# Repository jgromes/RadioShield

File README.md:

# Arduino Radio Shield

## "The Swiss Army Knife of Arduino Radio shields" - [Hackaday.com blog](https://hackaday.com/2018/07/28/why-have-only-one-radio-when-you-can-have-two/)

### Designed for use with [RadioLib](https://github.com/jgromes/RadioLib) - Universal wireless communication library for Arduino.

## Revision C
The latest hardware revision, compatible with both 5V and 3.3V Arduino boards. The entire project was also rebranded as Radio Shield!

Additional modules:
* **SIM800C** GSM module
* **CC1101** FSK module
* **nRF24L01** 2.4 GHz module

## Revision B
Added some improvements over rev. A, such as improved Arduino Mega support and interrupt selection pin header.

## Revision A
After a first few prototypes, rev. A is the first fully tested and working shield.  
Supported modules:
* **ESP8266** WiFi module
* **HC-05** Bluetooth module
* **RFM69** FSK/OOK radio module
* **SX127x** series LoRa modules - including SX1272, SX1276 and SX1278
* **XBee** modules (S2B)

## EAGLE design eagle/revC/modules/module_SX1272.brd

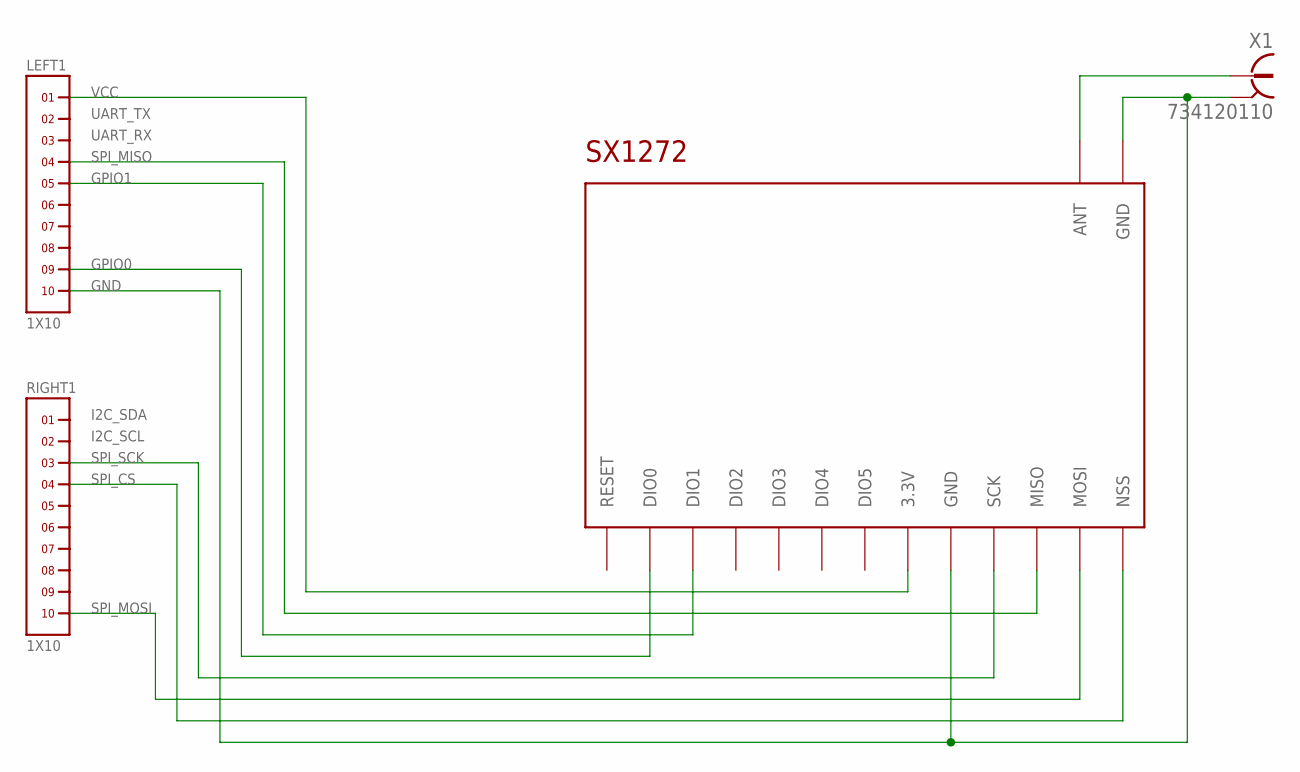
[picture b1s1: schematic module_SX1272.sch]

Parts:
LEFT1: 1X10
RIGHT1: 1X10
U$1: SX1272
X1: 734120110

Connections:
GND: LEFT1.10, U$1.GND@1 (GND), U$1.GND@2 (GND), X1.S@1 (2), X1.S@2 (2), X1.S@3 (2)
unnamed: U$1.ANT, X1.1
unnamed: LEFT1.9, U$1.DIO0
unnamed: RIGHT1.10, U$1.MOSI
unnamed: RIGHT1.4, U$1.NSS
unnamed: RIGHT1.3, U$1.SCK
unnamed: LEFT1.5, U$1.DIO1
unnamed: LEFT1.4, U$1.MISO
VCC: LEFT1.1, U$1.3.3V

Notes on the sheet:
VCC
UART_TX
UART_RX
SPI_MISO
GPIO1
GND
GPIO0
SPI_MOSI
I2C_SDA
I2C_SCL
SPI_SCK
SPI_CS

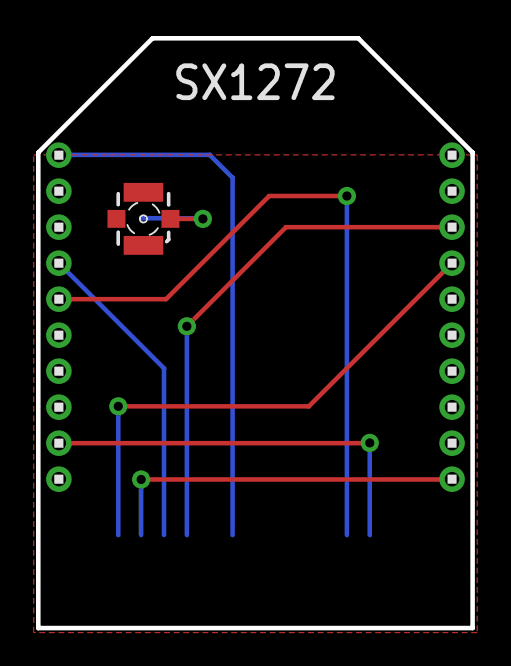
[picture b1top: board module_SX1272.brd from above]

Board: 2 copper layers, 24.1 x 32.8 mm, 4 parts (1 on the bottom side), 9 nets.

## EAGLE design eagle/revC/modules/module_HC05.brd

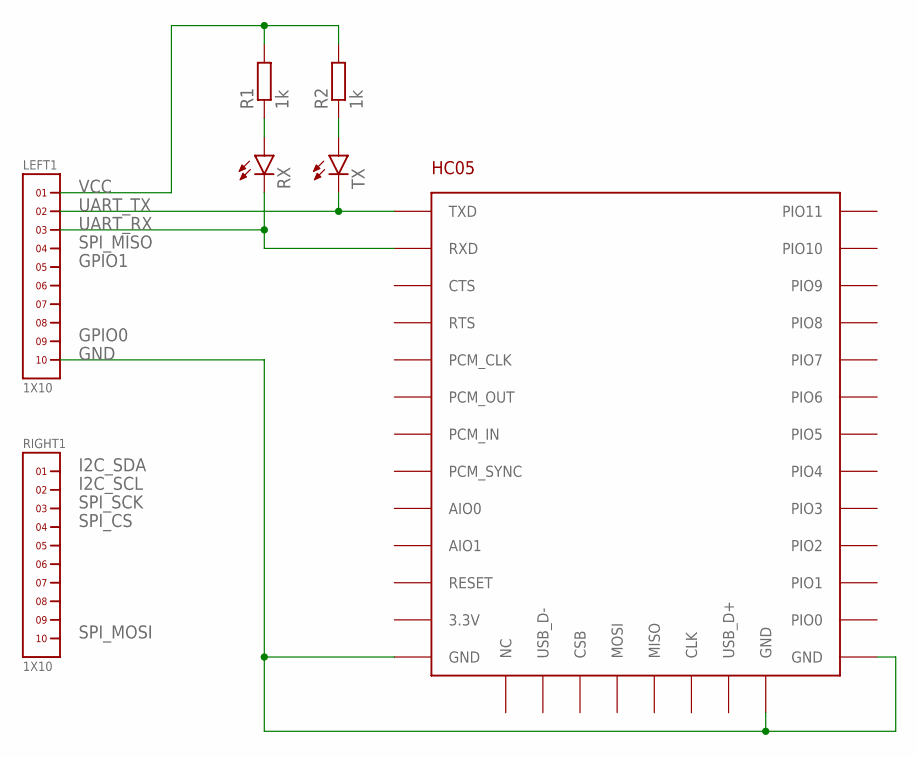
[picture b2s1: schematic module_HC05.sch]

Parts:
LEFT1: 1X10
R1, R2: 1k; R0603
RIGHT1: 1X10
RX: LEDCHIP-LED0603; CHIP-LED0603
TX: LEDCHIP-LED0603; CHIP-LED0603
U$1: HC05

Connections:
GND: LEFT1.10, U$1.GND@1 (GND), U$1.GND@2 (GND), U$1.GND@3 (GND)
unnamed: R2.1, TX.A
unnamed: R1.1, RX.A
unnamed: LEFT1.2, TX.C, U$1.TX (TXD)
unnamed: LEFT1.3, RX.C, U$1.RX (RXD)
VCC: LEFT1.1, R1.2, R2.2

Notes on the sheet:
VCC
I2C_SDA
I2C_SCL
SPI_SCK
SPI_CS
SPI_MOSI
UART_TX
UART_RX
SPI_MISO
GPIO1
GPIO0
GND

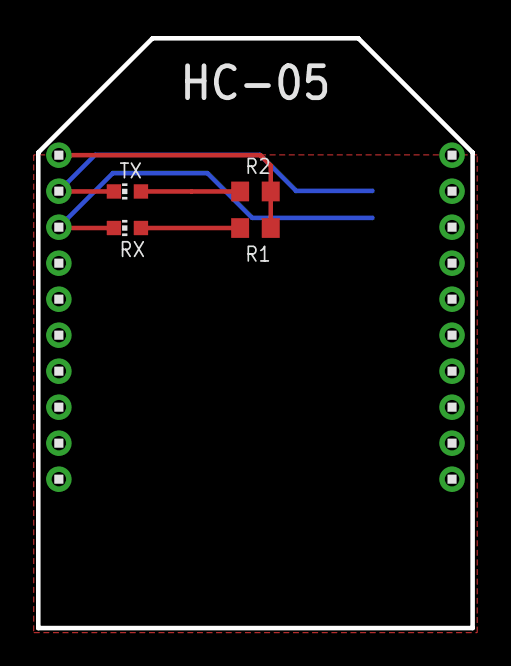
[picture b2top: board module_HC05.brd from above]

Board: 2 copper layers, 24.1 x 32.8 mm, 7 parts (1 on the bottom side), 6 nets.

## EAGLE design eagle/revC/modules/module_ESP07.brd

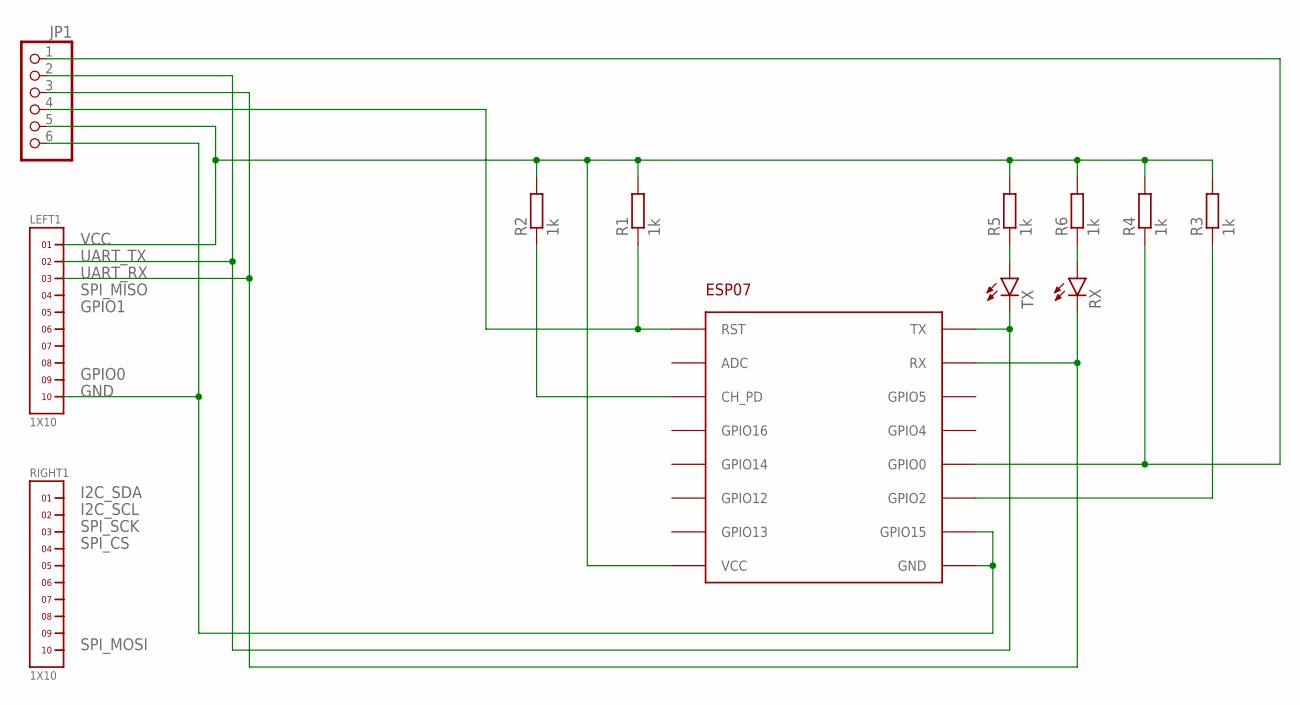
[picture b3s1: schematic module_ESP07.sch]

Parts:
JP1: PINHD-1X6; 1X06
LEFT1: 1X10
R1, R2, R3, R4, R5, R6: 1k; R0603
RIGHT1: 1X10
RX: LEDCHIPLED_0603; CHIPLED_0603
TX: LEDCHIPLED_0603; CHIPLED_0603
U$1: ESP-07; ESP07

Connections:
GND: JP1.6, LEFT1.10, U$1.GND, U$1.GPIO15
GPIO0: JP1.1, R4.1, U$1.GPIO0
unnamed: R6.1, RX.A
unnamed: R5.1, TX.A
unnamed: R2.1, U$1.CH_PD
unnamed: R3.1, U$1.GPIO2
RST: JP1.4, R1.1, U$1.RST
UART_RX: JP1.3, LEFT1.3, RX.C, U$1.RX
UART_TX: JP1.2, LEFT1.2, TX.C, U$1.TX
VCC: JP1.5, LEFT1.1, R1.2, R2.2, R3.2, R4.2, R5.2, R6.2, U$1.VCC

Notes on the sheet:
VCC
I2C_SDA
I2C_SCL
SPI_SCK
SPI_CS
SPI_MOSI
UART_TX
UART_RX
SPI_MISO
GPIO1
GPIO0
GND

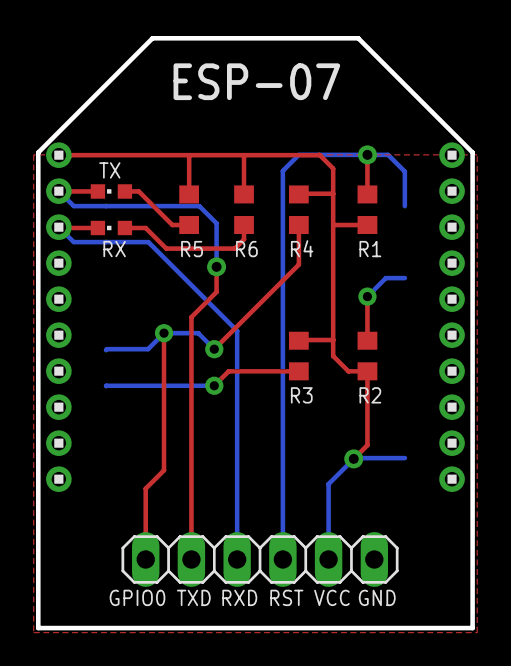
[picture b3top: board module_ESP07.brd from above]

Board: 2 copper layers, 24.1 x 32.8 mm, 12 parts (1 on the bottom side), 10 nets.

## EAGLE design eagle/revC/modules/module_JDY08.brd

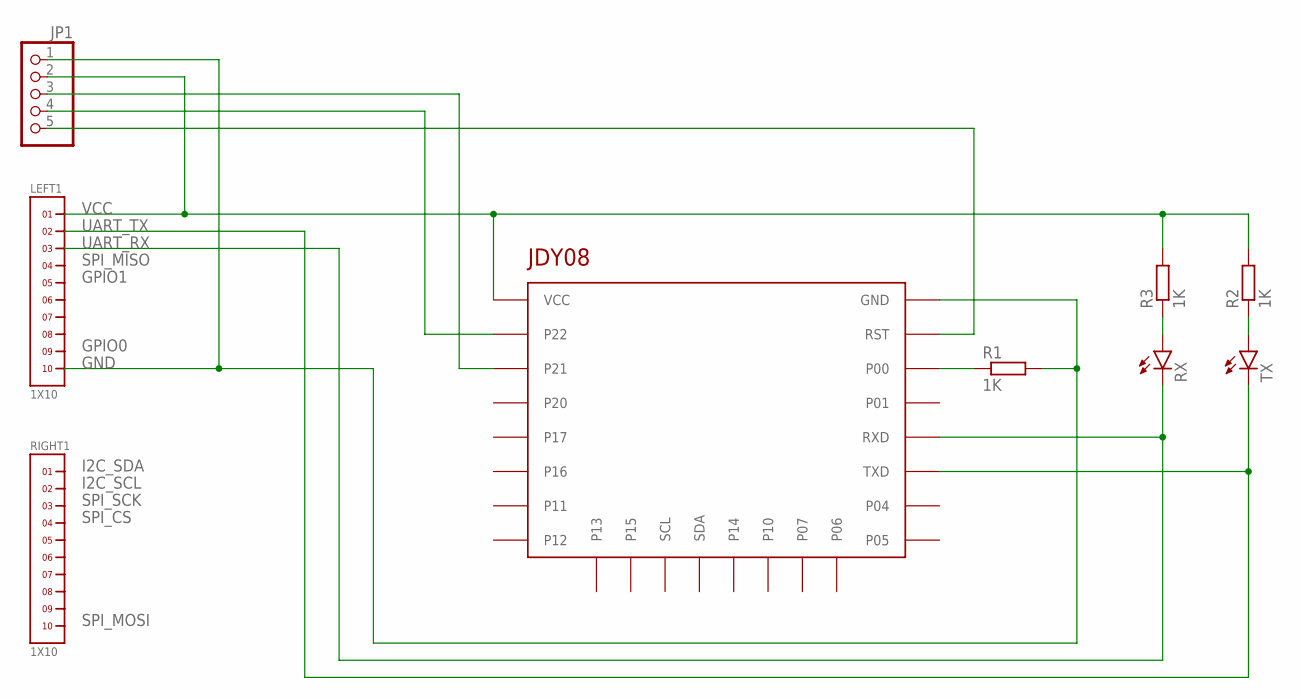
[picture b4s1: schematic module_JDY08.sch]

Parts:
JP1: PINHD-1X5; 1X05
LEFT1: 1X10
R1, R2, R3: 1K; R0603
RIGHT1: 1X10
RX: LEDCHIPLED_0603; CHIPLED_0603
TX: LEDCHIPLED_0603; CHIPLED_0603
U$1: JDY08

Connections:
GND: JP1.1, LEFT1.10, R1.2, U$1.GND
unnamed: JP1.5, U$1.RST
unnamed: JP1.3, U$1.P21
unnamed: JP1.4, U$1.P22
unnamed: LEFT1.3, RX.C, U$1.RXD
unnamed: R2.1, TX.A
unnamed: R3.1, RX.A
unnamed: R1.1, U$1.P00
unnamed: LEFT1.2, TX.C, U$1.TXD
VCC: JP1.2, LEFT1.1, R2.2, R3.2, U$1.VCC

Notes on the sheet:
VCC
I2C_SDA
I2C_SCL
SPI_SCK
SPI_CS
SPI_MOSI
UART_TX
UART_RX
SPI_MISO
GPIO1
GPIO0
GND

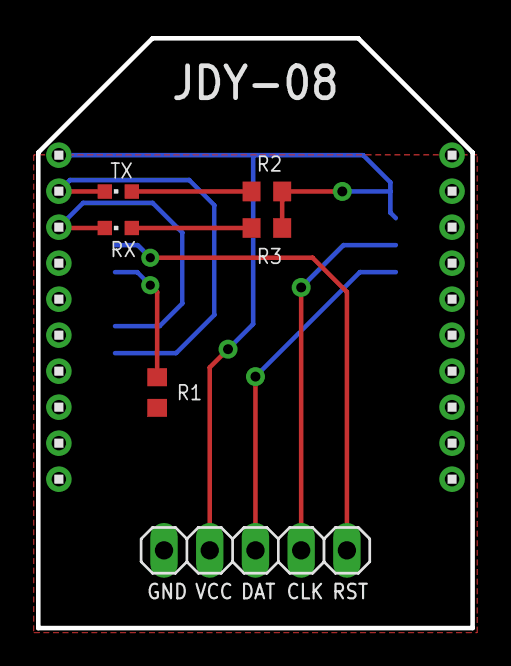
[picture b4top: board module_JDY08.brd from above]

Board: 2 copper layers, 24.1 x 32.8 mm, 9 parts (1 on the bottom side), 10 nets.

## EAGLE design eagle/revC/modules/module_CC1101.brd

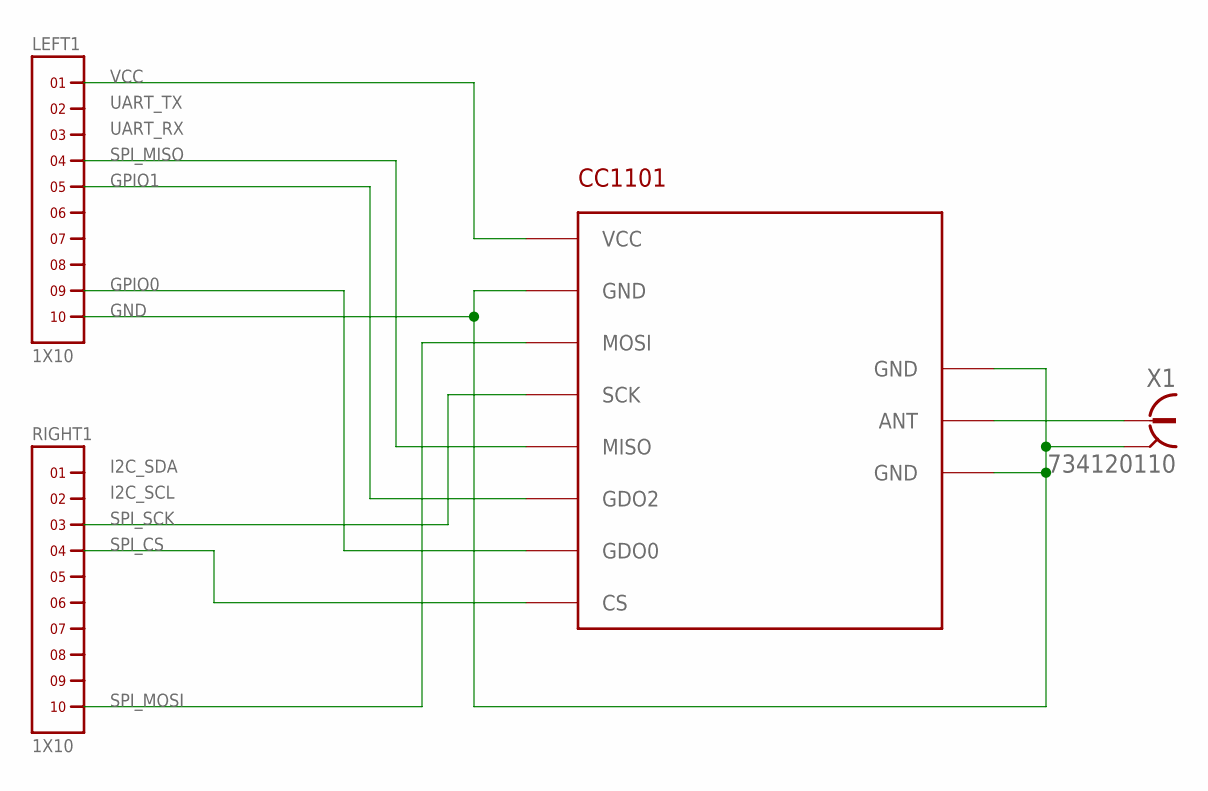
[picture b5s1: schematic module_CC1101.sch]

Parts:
CC1101: CC1101
LEFT1: 1X10
RIGHT1: 1X10
X1: 734120110

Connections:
GND: CC1101.GND@1 (GND), CC1101.GND@2 (GND), CC1101.GND@3 (GND), LEFT1.10, X1.S@1 (2), X1.S@2 (2), X1.S@3 (2)
INT0: CC1101.GDO0, LEFT1.9
INT1: CC1101.GDO2, LEFT1.5
unnamed: CC1101.ANT, X1.1
SPI_CS: CC1101.CS, RIGHT1.4
SPI_MISO: CC1101.MISO, LEFT1.4
SPI_MOSI: CC1101.MOSI, RIGHT1.10
SPI_SCK: CC1101.SCK, RIGHT1.3
VCC: CC1101.VCC, LEFT1.1

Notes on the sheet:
VCC
UART_TX
UART_RX
SPI_MISO
GPIO1
GND
GPIO0
SPI_MOSI
I2C_SDA
I2C_SCL
SPI_SCK
SPI_CS

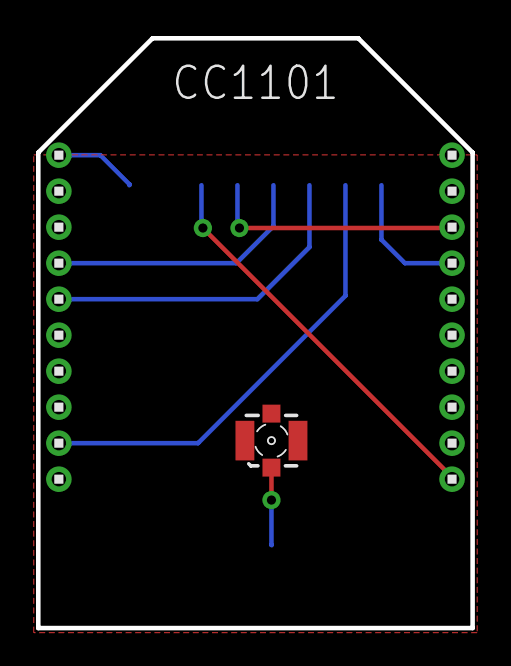
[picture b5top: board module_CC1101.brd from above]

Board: 2 copper layers, 24.1 x 32.8 mm, 4 parts (1 on the bottom side), 9 nets.

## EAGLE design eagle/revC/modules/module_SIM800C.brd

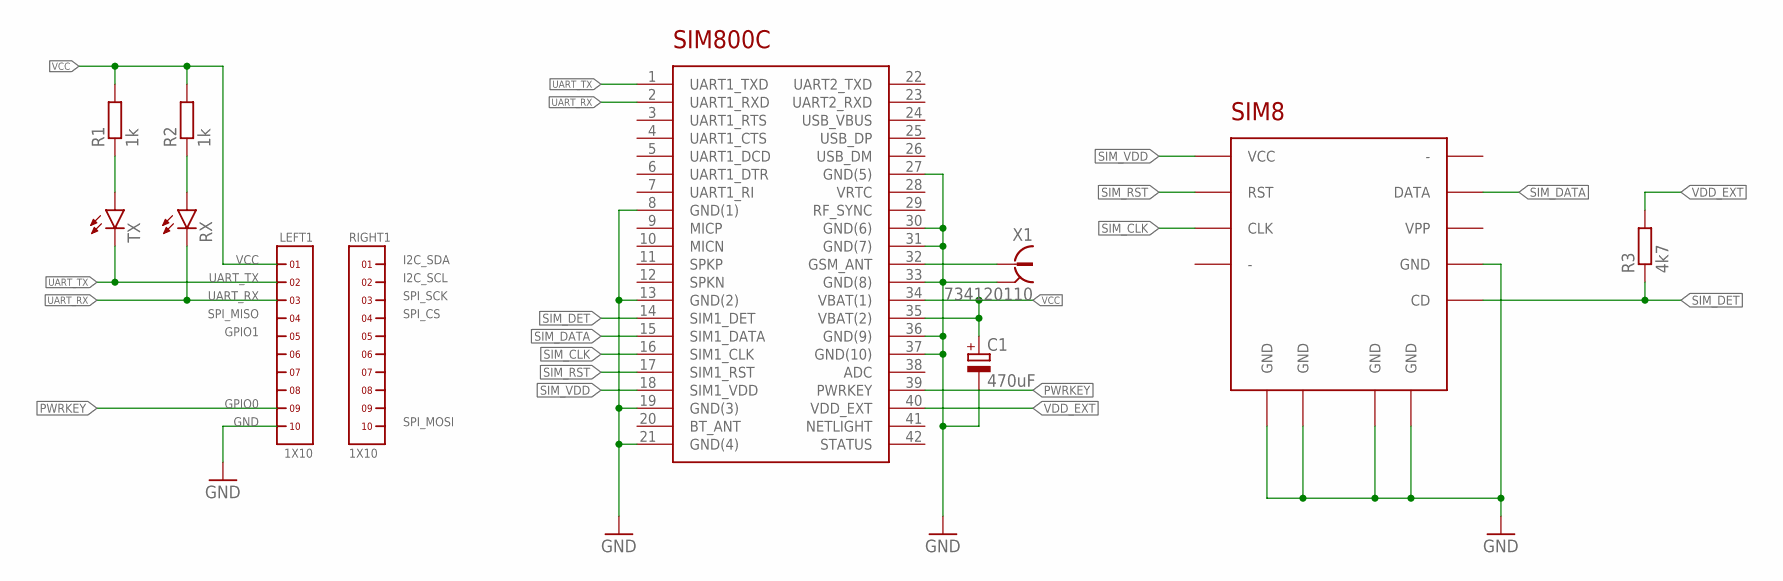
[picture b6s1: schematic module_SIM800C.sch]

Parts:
C1: 470uF; SMC_D
IC1: SIM800C
LEFT1: 1X10
R1, R2: 1k; R0603
R3: 4k7; R0603
RIGHT1: 1X10
RX: LEDCHIPLED_0603; CHIPLED_0603
TX: LEDCHIPLED_0603; CHIPLED_0603
U$2: 115Q-BCA0
X1: 734120110

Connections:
GND: C1.-, IC1.8 (GND(1)), IC1.13 (GND(2)), IC1.19 (GND(3)), IC1.21 (GND(4)), IC1.27 (GND(5)), IC1.30 (GND(6)), IC1.31 (GND(7)), IC1.33 (GND(8)), IC1.36 (GND(9)), IC1.37 (GND(10)), LEFT1.10, U$2.P$5 (GND), U$2.P$10 (GND), U$2.P$11 (GND), U$2.P$12 (GND), U$2.P$13 (GND), X1.S@1 (2), X1.S@2 (2), X1.S@3 (2)
unnamed: IC1.32 (GSM_ANT), X1.1
unnamed: R1.1, TX.A
unnamed: R2.1, RX.A
PWRKEY: IC1.39 (PWRKEY), LEFT1.9
SIM_CLK: IC1.16 (SIM1_CLK), U$2.P$3 (CLK)
SIM_DATA: IC1.15 (SIM1_DATA), U$2.P$7 (DATA)
SIM_DET: IC1.14 (SIM1_DET), R3.1, U$2.P$9 (CD)
SIM_RST: IC1.17 (SIM1_RST), U$2.P$2 (RST)
SIM_VDD: IC1.18 (SIM1_VDD), U$2.P$1 (VCC)
UART_RX: IC1.2 (UART1_RXD), LEFT1.3, RX.C
UART_TX: IC1.1 (UART1_TXD), LEFT1.2, TX.C
VCC: C1.+, IC1.34 (VBAT(1)), IC1.35 (VBAT(2)), LEFT1.1, R1.2, R2.2
VDD_EXT: IC1.40 (VDD_EXT), R3.2

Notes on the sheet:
VCC
UART_TX
UART_RX
SPI_MISO
GPIO1
GND
GPIO0
SPI_MOSI
I2C_SDA
I2C_SCL
SPI_SCK
SPI_CS

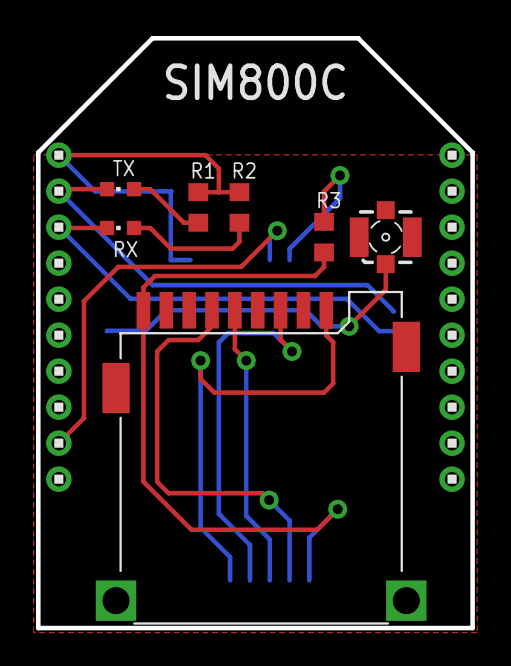
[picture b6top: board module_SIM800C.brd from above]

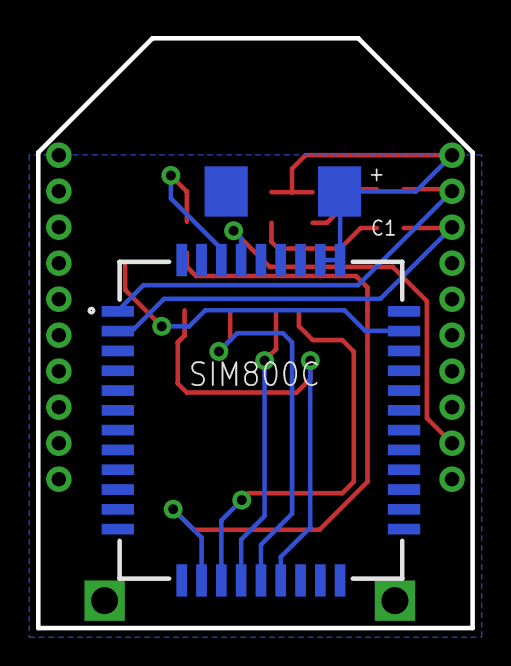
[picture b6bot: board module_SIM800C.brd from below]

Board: 2 copper layers, 24.1 x 32.8 mm, 11 parts (2 on the bottom side), 14 nets.

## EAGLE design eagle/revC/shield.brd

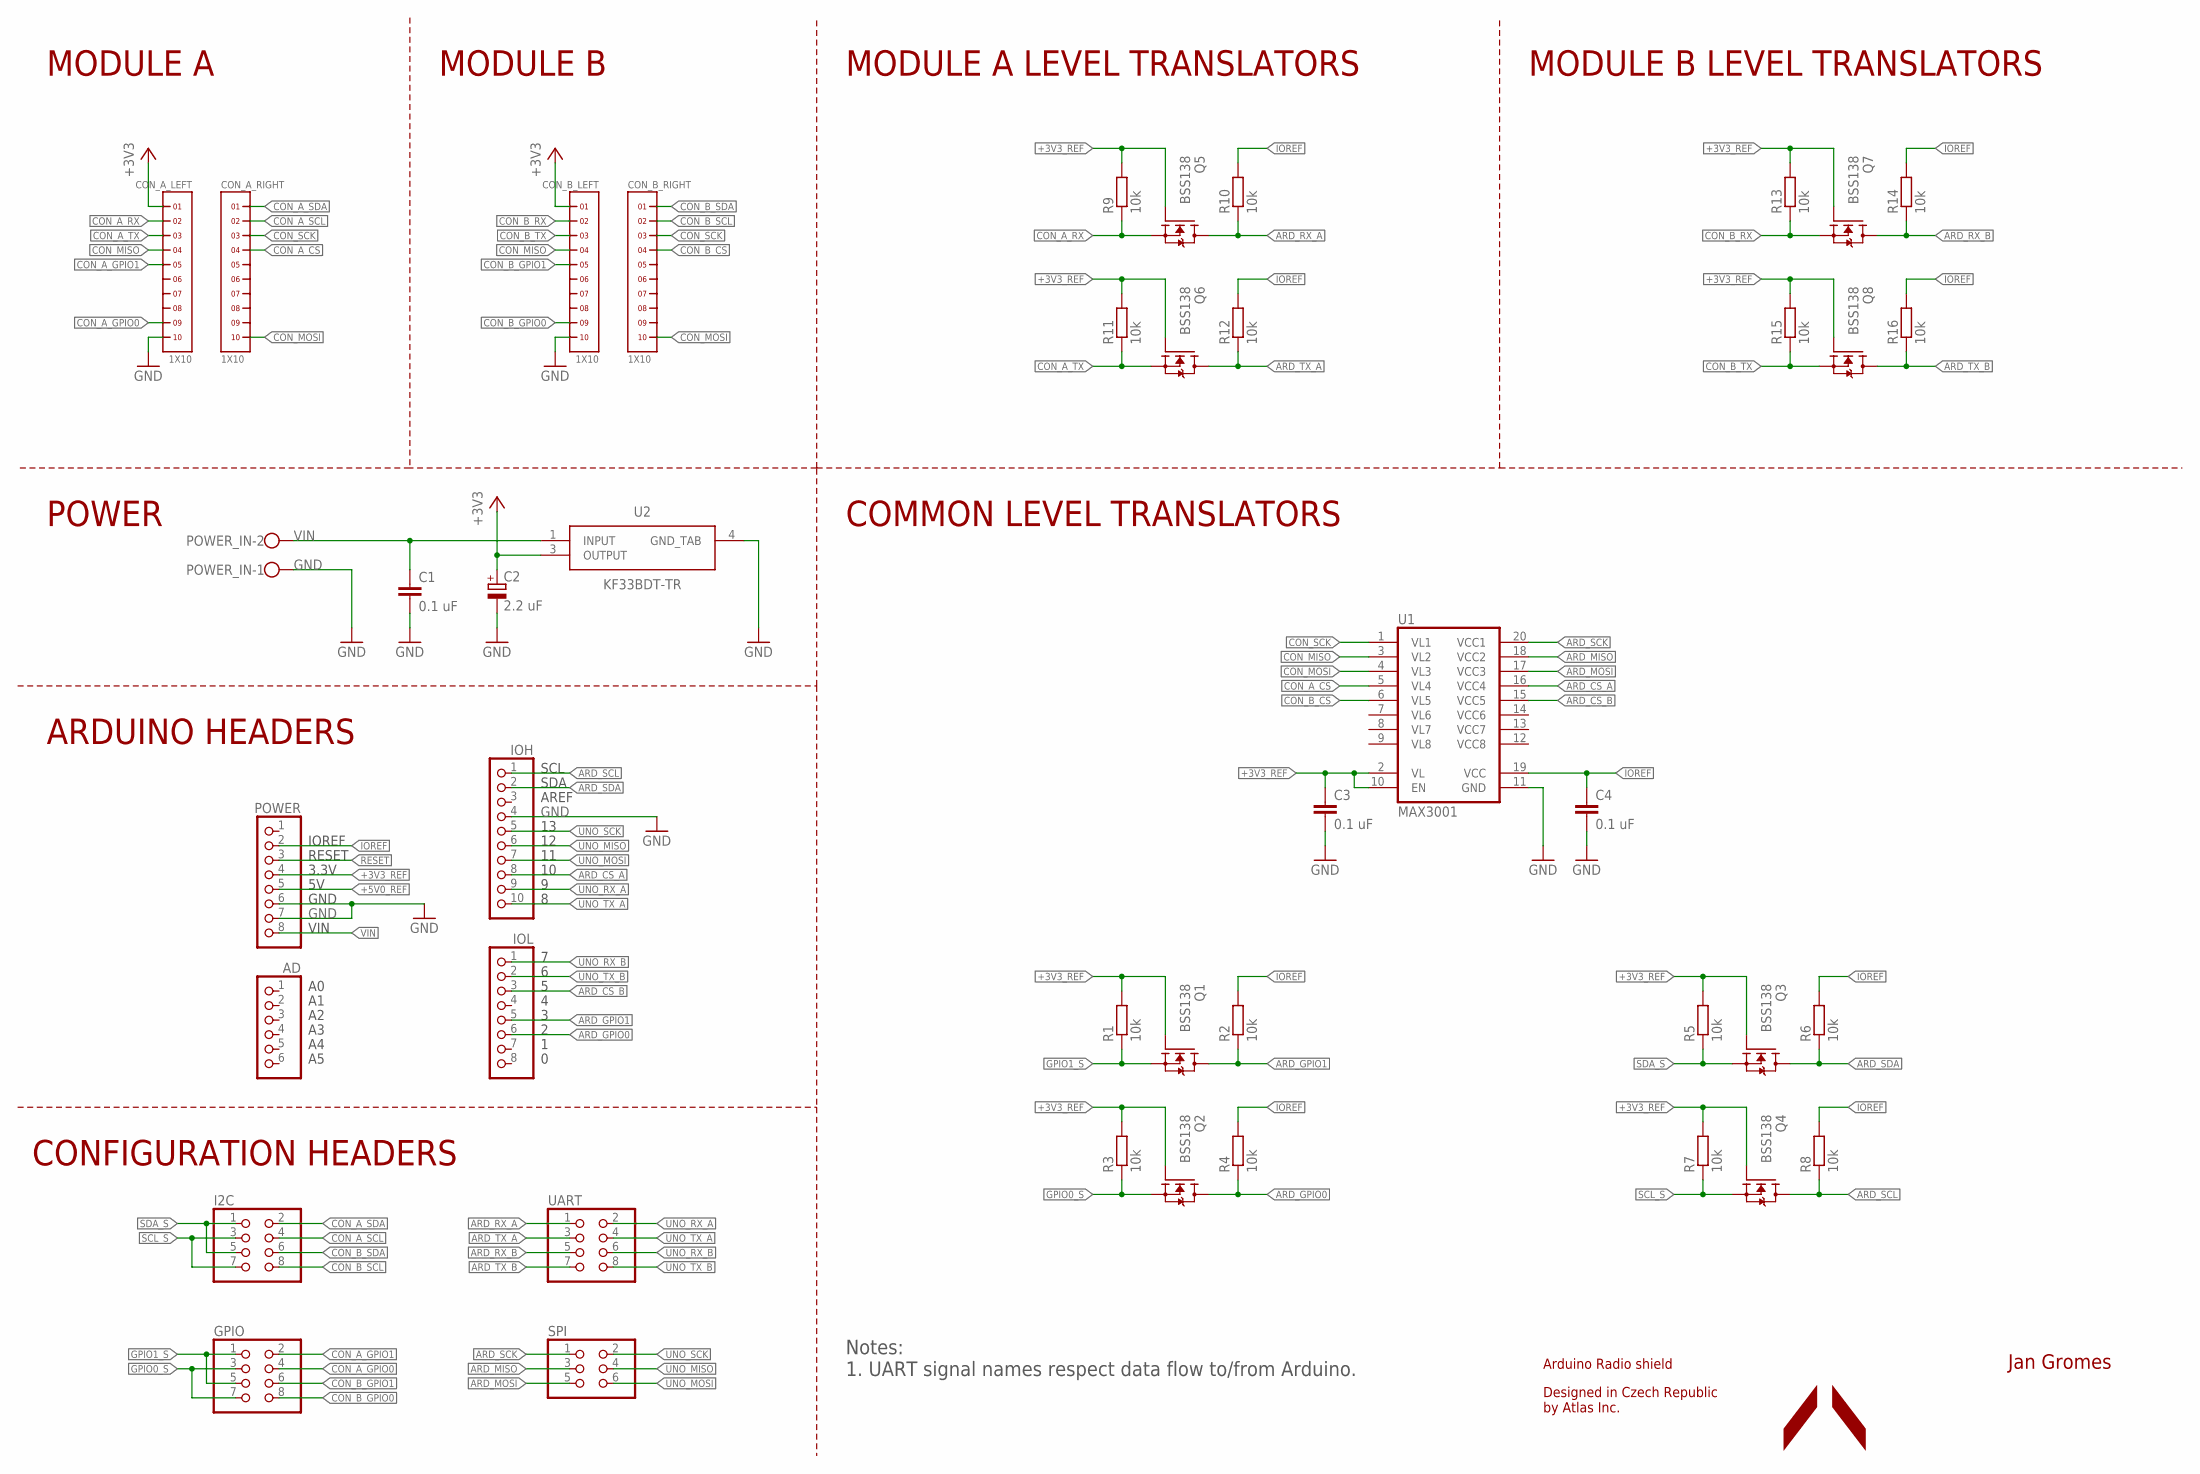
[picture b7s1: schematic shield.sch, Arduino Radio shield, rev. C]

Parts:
AD: PINHD-1X6; 1X06
C1, C3, C4: 0.1 uF; C0603
C2: 2.2 uF; SMC_A
CON_A_LEFT: 1X10
CON_A_RIGHT: 1X10
CON_B_LEFT: 1X10
CON_B_RIGHT: 1X10
GPIO: PINHD-2X4; 2X04
I2C: PINHD-2X4; 2X04
IOH: PINHD-1X10; 1X10
IOL: PINHD-1X8; 1X08
POWER: PINHD-1X8; 1X08
POWER_IN: W237-102
Q1, Q2, Q3, Q4, Q5, Q6, Q7, Q8: BSS138; SOT23
R1, R2, R3, R4, R5, R6, R7, R8, R9, R10, R11, R12, R13, R14, R15, R16: 10k; R0603
SPI: PINHD-2X3; 2X03
U1: MAX3001; TSSOP20
U2: KF33BDT-TR; TO228P972X240-3N
UART: PINHD-2X4; 2X04

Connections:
+3V3: C2.+, CON_A_LEFT.1, CON_B_LEFT.1, U2.3 (OUTPUT)
+3V3_REF: C3.1, POWER.4, Q1.1 (G), Q2.1 (G), Q3.1 (G), Q4.1 (G), Q5.1 (G), Q6.1 (G), Q7.1 (G), Q8.1 (G), R1.2, R3.2, R5.2, R7.2, R9.2, R11.2, R13.2, R15.2, U1.2 (VL), U1.10 (EN)
+5V0_REF: POWER.5
ARD_CS_A: IOH.8, U1.16 (VCC4)
ARD_CS_B: IOL.3, U1.15 (VCC5)
ARD_GPIO0: IOL.6, Q2.3 (D), R4.1
ARD_GPIO1: IOL.5, Q1.3 (D), R2.1
ARD_MISO: SPI.3, U1.18 (VCC2)
ARD_MOSI: SPI.5, U1.17 (VCC3)
ARD_RX_A: Q5.3 (D), R10.1, UART.1
ARD_RX_B: Q7.3 (D), R14.1, UART.5
ARD_SCK: SPI.1, U1.20 (VCC1)
ARD_SCL: IOH.1, Q4.3 (D), R8.1
ARD_SDA: IOH.2, Q3.3 (D), R6.1
ARD_TX_A: Q6.3 (D), R12.1, UART.3
ARD_TX_B: Q8.3 (D), R16.1, UART.7
CON_A_CS: CON_A_RIGHT.4, U1.5 (VL4)
CON_A_GPIO0: CON_A_LEFT.9, GPIO.4
CON_A_GPIO1: CON_A_LEFT.5, GPIO.2
CON_A_RX: CON_A_LEFT.2, Q5.2 (S), R9.1
CON_A_SCL: CON_A_RIGHT.2, I2C.4
CON_A_SDA: CON_A_RIGHT.1, I2C.2
CON_A_TX: CON_A_LEFT.3, Q6.2 (S), R11.1
CON_B_CS: CON_B_RIGHT.4, U1.6 (VL5)
CON_B_GPIO0: CON_B_LEFT.9, GPIO.8
CON_B_GPIO1: CON_B_LEFT.5, GPIO.6
CON_B_RX: CON_B_LEFT.2, Q7.2 (S), R13.1
CON_B_SCL: CON_B_RIGHT.2, I2C.8
CON_B_SDA: CON_B_RIGHT.1, I2C.6
CON_B_TX: CON_B_LEFT.3, Q8.2 (S), R15.1
CON_MISO: CON_A_LEFT.4, CON_B_LEFT.4, U1.3 (VL2)
CON_MOSI: CON_A_RIGHT.10, CON_B_RIGHT.10, U1.4 (VL3)
CON_SCK: CON_A_RIGHT.3, CON_B_RIGHT.3, U1.1 (VL1)
GND: C1.2, C2.-, C3.2, C4.2, CON_A_LEFT.10, CON_B_LEFT.10, IOH.4, POWER.6, POWER.7, POWER_IN.1, U1.11 (GND), U2.4 (GND_TAB)
GPIO0_S: GPIO.3, GPIO.7, Q2.2 (S), R3.1
GPIO1_S: GPIO.1, GPIO.5, Q1.2 (S), R1.1
IOREF: C4.1, POWER.2, R2.2, R4.2, R6.2, R8.2, R10.2, R12.2, R14.2, R16.2, U1.19 (VCC)
RESET: POWER.3
SCL_S: I2C.3, I2C.7, Q4.2 (S), R7.1
SDA_S: I2C.1, I2C.5, Q3.2 (S), R5.1
UNO_MISO: IOH.6, SPI.4
UNO_MOSI: IOH.7, SPI.6
UNO_RX_A: IOH.9, UART.2
UNO_RX_B: IOL.1, UART.6
UNO_SCK: IOH.5, SPI.2
UNO_TX_A: IOH.10, UART.4
UNO_TX_B: IOL.2, UART.8
VIN: C1.1, POWER.8, POWER_IN.2, U2.1 (INPUT)

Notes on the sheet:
Jan Gromes
AREF
SDA
SCL
VIN
GND
3.3V
RESET
IOREF
MODULE B LEVEL TRANSLATORS
MODULE A LEVEL TRANSLATORS
MODULE A
MODULE B
POWER
ARDUINO HEADERS
Arduino Radio shield
Designed in Czech Republic by Atlas Inc.
CONFIGURATION HEADERS
COMMON LEVEL TRANSLATORS
Notes: 1. UART signal names respect data flow to/from Arduino.

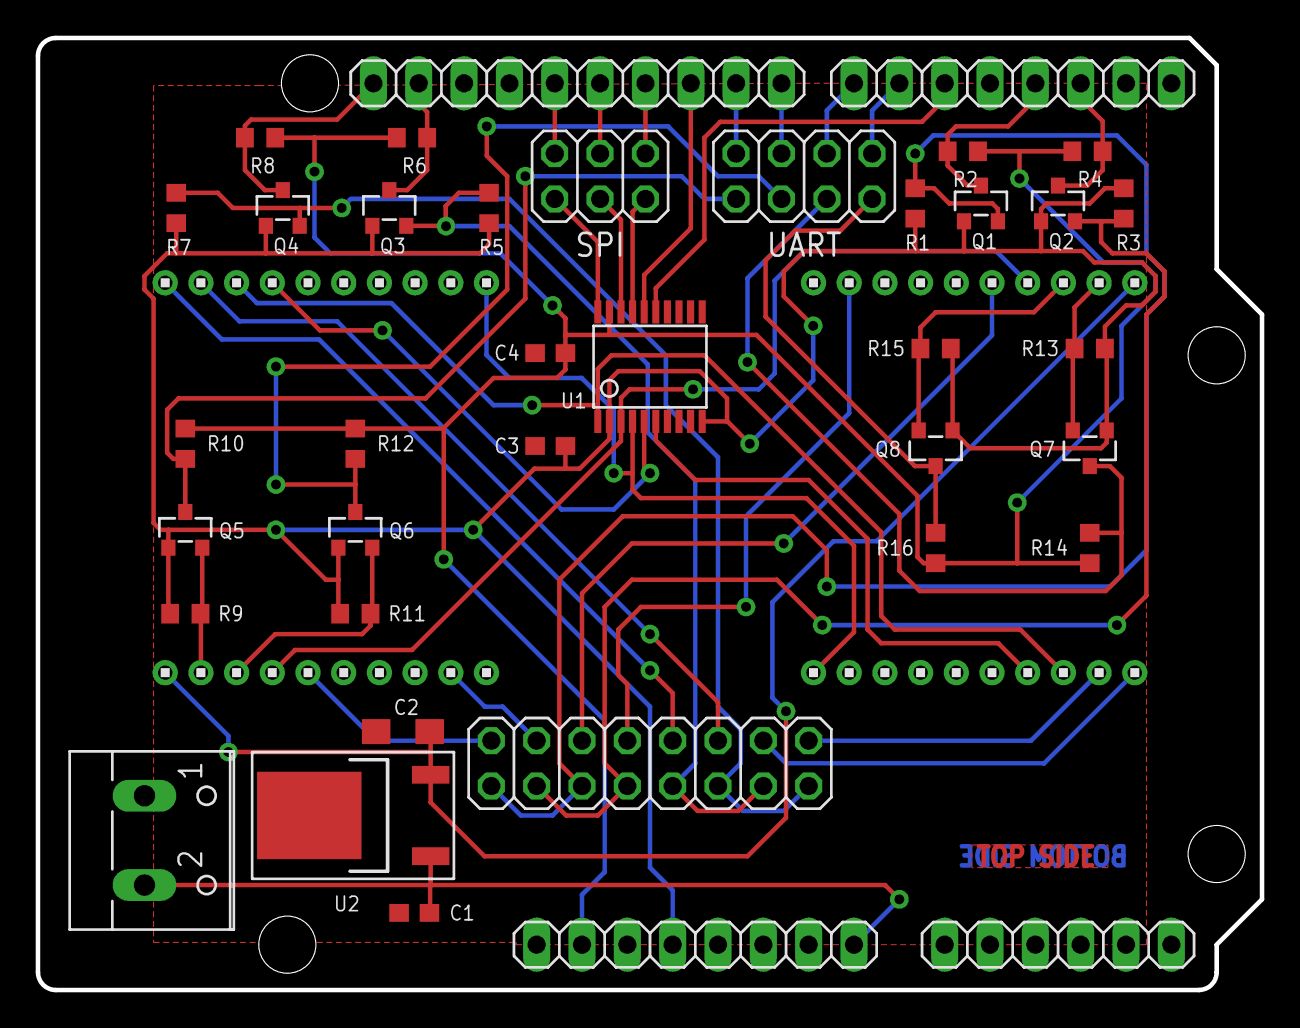
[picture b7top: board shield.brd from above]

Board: 2 copper layers, 68.6 x 53.3 mm, 43 parts (0 on the bottom side), 46 nets.

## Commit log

2018-07-14 Added images
2018-07-14 Added gitignore
2018-07-14 Updated svg drawing
2018-07-14 Updated gitignore
2018-07-14 Added Eagle files for revision A
2018-07-15 Added gitattributes
2018-07-15 Added SX1272/78 images
2018-07-15 Added RF69 images
2018-07-15 Added HC05 images
2018-07-15 Updated HC05 drawing
2018-07-15 Added ESP07 images
2018-07-15 Added license
2018-07-17 Added eagle files for shield rev.B
2018-07-17 Added eagle files for JDY-08 Bluetooth breakout board
2018-07-17 Added eagle files for SX1272 breakout board
2018-07-17 Updated SX1272 layout
2018-07-17 Added eagle files for HC-05
2018-07-19 Added eagle files for SX1278
2018-07-20 Added eagle files for ESP-07
2018-07-20 Added eagle files for RF69
2018-07-29 Added rev.B shield drawings
2018-07-29 Moved shield rev.B drawing
2018-07-29 ESP8266 - Added indication LEDs
2019-01-08 Added eagle files for SIM800C
2019-01-08 [SIM800C] Updated layout
2019-01-26 Added rev. C eagle files
2019-01-27 Added rev.C drawings
2019-01-27 [SIM800C] Added eagle files and drawings
2019-02-10 [SIM800C] Added PWRKEY connection
2019-02-10 [SIM800C] Fixed incorrect SIM slot wiring
2019-02-10 [SIM800] Added SIM detection pullup
2019-05-27 Added module library
2019-05-27 Replaced modules with library parts
2019-05-27 Added SX1262 breakout
2019-06-18 Fixed module name layers
